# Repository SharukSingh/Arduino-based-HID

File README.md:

# H.U.S.K.Y.

An IO device to interact with your computer.

Arduino and Python code along with PCB design included

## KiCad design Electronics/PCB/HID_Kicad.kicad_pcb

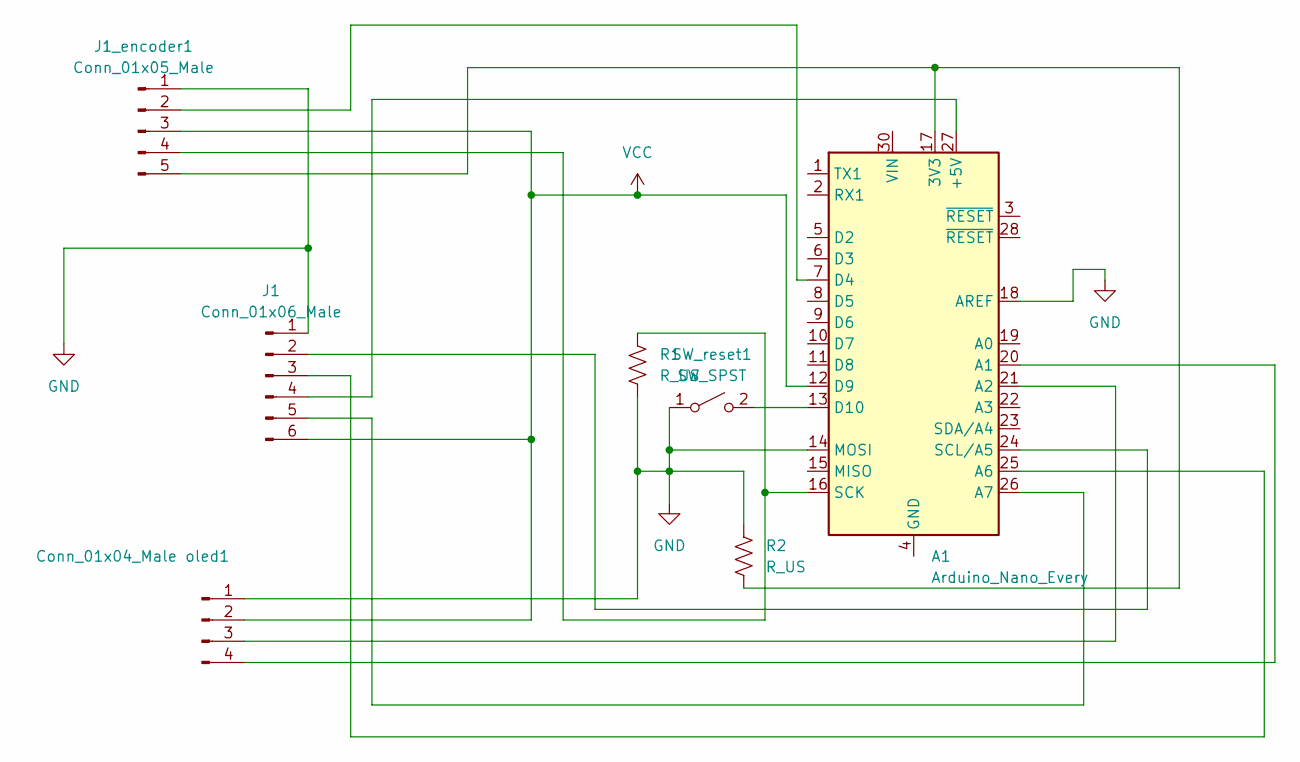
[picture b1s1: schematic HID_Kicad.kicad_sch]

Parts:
A1: Arduino_Nano_Every; Arduino_Nano
J1: Conn_01x06_Male; SolderWire-0.5sqmm_1x06_P4.8mm_D0.9mm_OD2.3mm
J1_encoder1: Conn_01x05_Male; SolderWire-0.5sqmm_1x05_P4.8mm_D0.9mm_OD2.3mm
R1, R2: R_US; R_Axial_DIN0309_L9.0mm_D3.2mm_P12.70mm_Horizontal
SW_reset1: SW_SPST; SW_TH_Tactile_Omron_B3F-10xx
oled1: Conn_01x04_Male; SolderWire-0.5sqmm_1x04_P4.6mm_D0.9mm_OD2.1mm

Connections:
GND: A1.14 (MOSI), A1.18 (AREF), J1.1, J1_encoder1.1, R1.2, R2.1, SW_reset1.1 (A), oled1.1
unnamed: A1.7 (D4), J1_encoder1.2
unnamed: A1.13 (D10), SW_reset1.2 (B)
unnamed: A1.16 (SCK), J1_encoder1.4, R1.1
unnamed: A1.20 (A1), oled1.4
unnamed: A1.24 (SCL/A5), J1.2
unnamed: A1.25 (A6), J1.3
unnamed: A1.26 (A7), J1.5
unnamed: A1.27 (+5V), J1.4
unnamed: A1.4 (GND), A1.29 (GND)
unnamed: A1.17 (3V3), J1_encoder1.5, R2.2
unnamed: A1.21 (A2), oled1.3
VCC: A1.12 (D9), J1.6, J1_encoder1.3, oled1.2

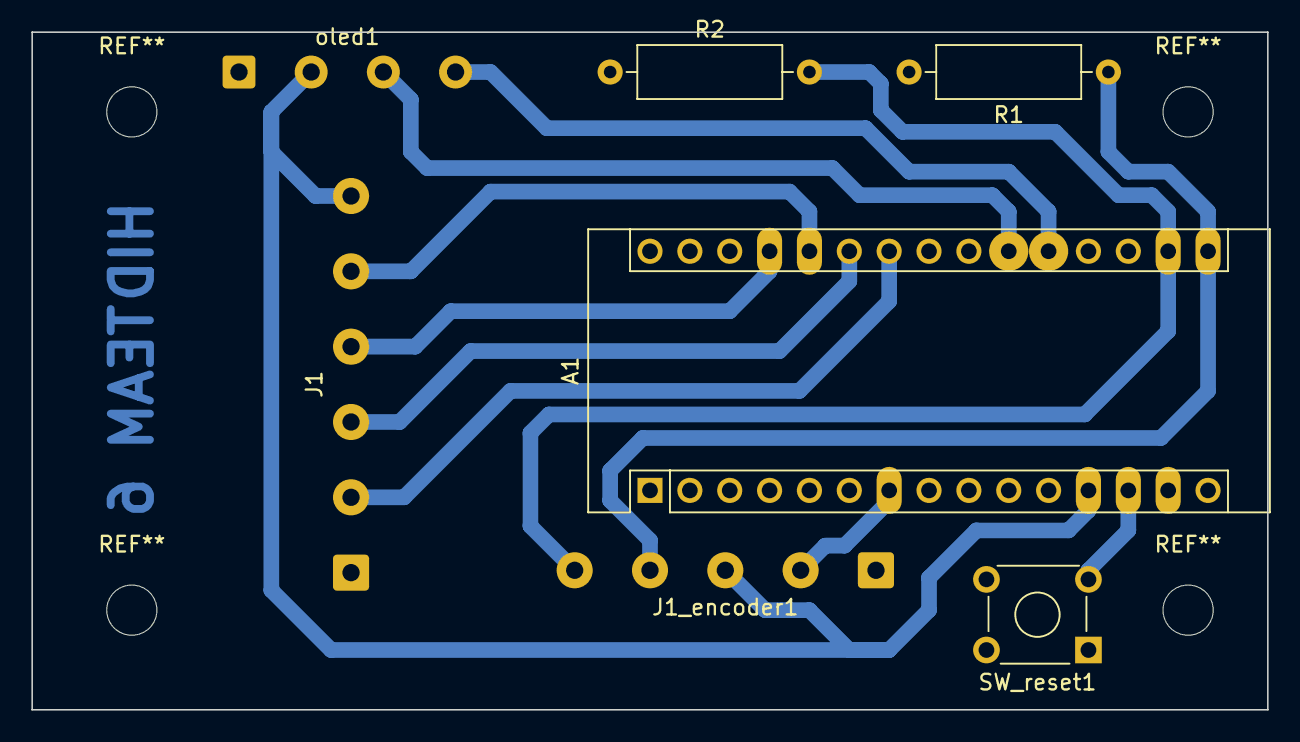
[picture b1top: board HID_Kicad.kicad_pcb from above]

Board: 2 copper layers, 78.7 x 43.2 mm, 7 parts (0 on the bottom side), 13 nets.

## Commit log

2022-07-06 added .gitignore
2022-07-07 updated pcb layout, added vcc for switches
2022-07-09 PCB design updated to fit inside enclosure
2023-02-25 added readme
